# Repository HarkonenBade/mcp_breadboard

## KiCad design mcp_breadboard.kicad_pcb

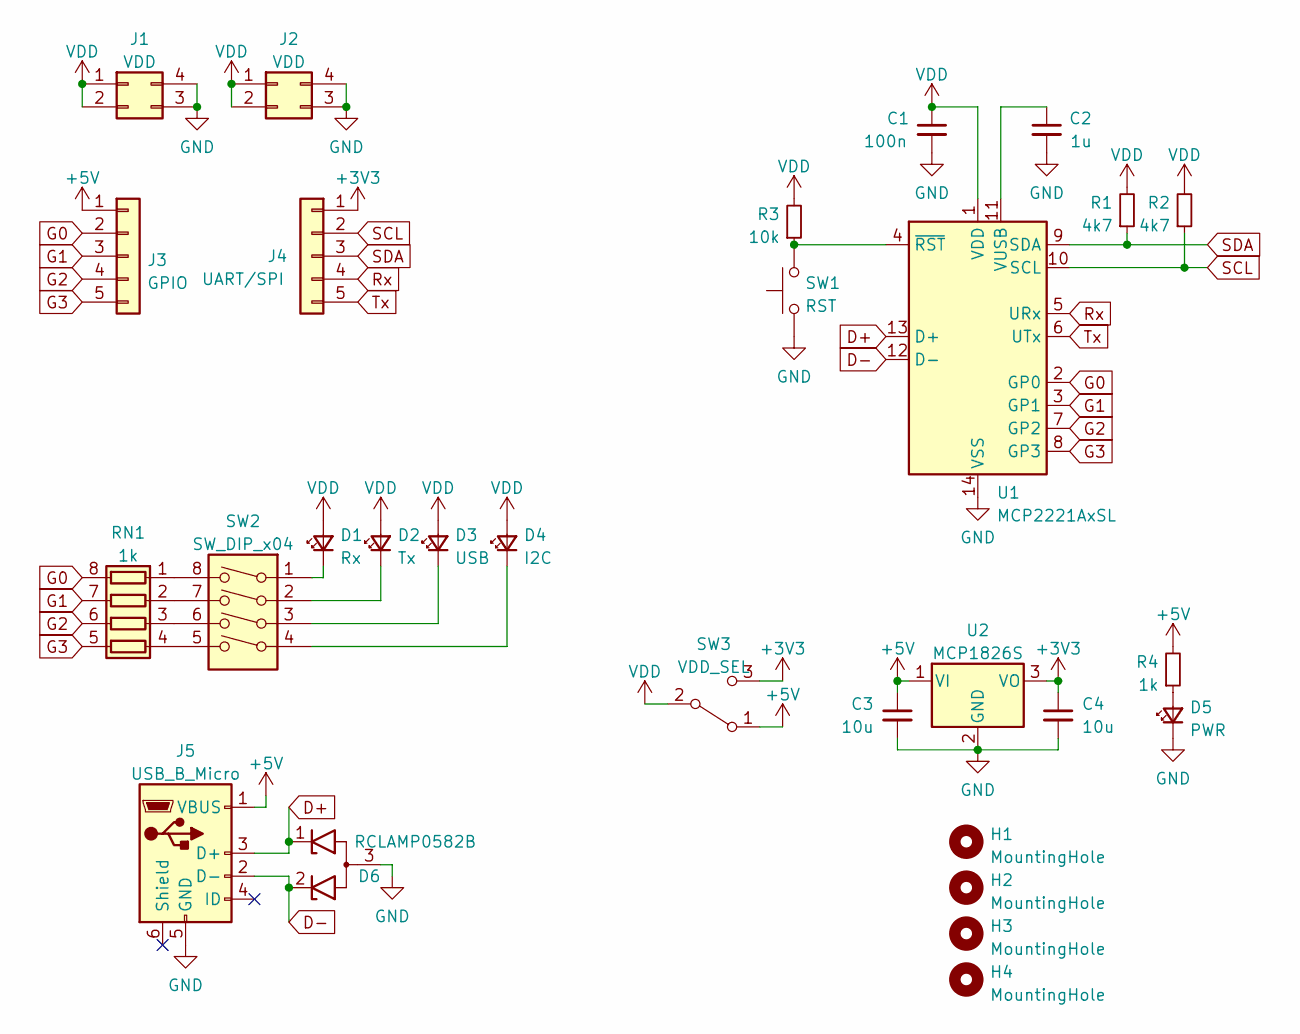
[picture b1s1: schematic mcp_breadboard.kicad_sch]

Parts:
C1: 100n; C_0603_1608Metric
C2: 1u; C_0603_1608Metric
C3, C4: 10u; C_0805_2012Metric; LCSC C1713
D1: Rx; LED_0805_2012Metric
D2: Tx; LED_0805_2012Metric
D3: USB; LED_0805_2012Metric
D4: I2C; LED_0805_2012Metric
D5: PWR; LED_0805_2012Metric
D6: RCLAMP0582B; SOT-523; LCSC C117553
H1, H2, H3, H4: MountingHole; MountingHole_2.7mm_M2.5_ISO7380
J1, J2: VDD; PinHeader_2x02_P2.54mm_Vertical
J3: GPIO; PinHeader_1x05_P2.54mm_Vertical
J4: UART/SPI; PinHeader_1x05_P2.54mm_Vertical
J5: USB_B_Micro; USB_Micro-B_Molex-105017-0001
R1, R2: 4k7; R_0603_1608Metric
R3: 10k; R_0603_1608Metric
R4: 1k; R_0603_1608Metric
RN1: 1k; R_Array_Convex_4x0603; LCSC C425239
SW1: RST; SW_Push_1P1T_NO_6x6mm_H9.5mm; LCSC C493020
SW2: SW_DIP_x04; SW_DIP_SPSTx04_Slide_6.7x11.72mm_W8.61mm_P2.54mm_LowProfile; LCSC C437204
SW3: VDD_SEL; PinHeader_1x03_P2.54mm_Vertical
U1: MCP2221AxSL; SOIC-14_3.9x8.7mm_P1.27mm
U2: MCP1826S; SOT-223-3_TabPin2; LCSC C150719

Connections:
+3V3: C4.1, J4.1, SW3.3 (C), U2.3 (VO)
+5V: C3.1, J3.1, J5.1 (VBUS), R4.2, SW3.1 (A), U2.1 (VI)
D+: D6.1 (K1), J5.3 (D+), U1.13 (D+)
D-: D6.2 (K2), J5.2 (D-), U1.12 (D-)
G0: J3.2, RN1.8 (R1.2), U1.2 (GP0)
G1: J3.3, RN1.7 (R2.2), U1.3 (GP1)
G2: J3.4, RN1.6 (R3.2), U1.7 (GP2)
G3: J3.5, RN1.5 (R4.2), U1.8 (GP3)
GND: C1.2, C2.2, C3.2, C4.2, D5.1 (K), D6.3 (A), J1.3, J1.4, J2.3, J2.4, J5.5 (GND), SW1.1, U1.14 (VSS), U2.2 (GND)
unnamed: C2.1, U1.11 (VUSB)
unnamed: D1.1 (K), SW2.1
unnamed: D2.1 (K), SW2.2
unnamed: D3.1 (K), SW2.3
unnamed: D4.1 (K), SW2.4
unnamed: D5.2 (A), R4.1
unnamed: R3.1, SW1.2, U1.4 (~RST)
unnamed: RN1.1 (R1.1), SW2.8
unnamed: RN1.2 (R2.1), SW2.7
unnamed: RN1.3 (R3.1), SW2.6
unnamed: RN1.4 (R4.1), SW2.5
Rx: J4.4, U1.5 (URx)
SCL: J4.2, R2.1, U1.10 (SCL)
SDA: J4.3, R1.1, U1.9 (SDA)
Tx: J4.5, U1.6 (UTx)
VDD: C1.1, D1.2 (A), D2.2 (A), D3.2 (A), D4.2 (A), J1.1, J1.2, J2.1, J2.2, R1.2, R2.2, R3.2, SW3.2 (B), U1.1 (VDD)

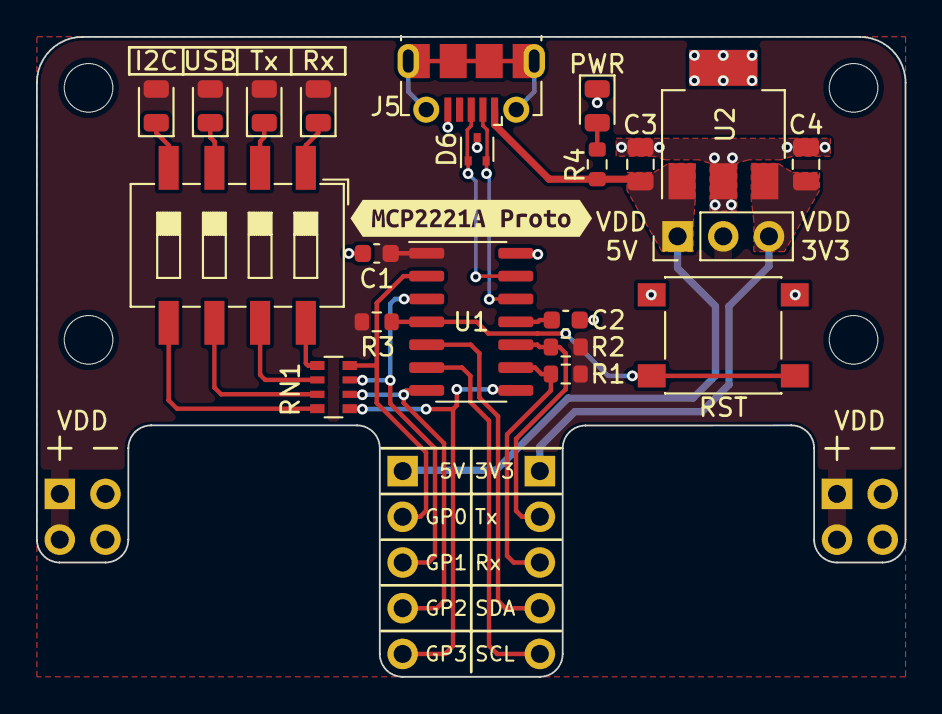
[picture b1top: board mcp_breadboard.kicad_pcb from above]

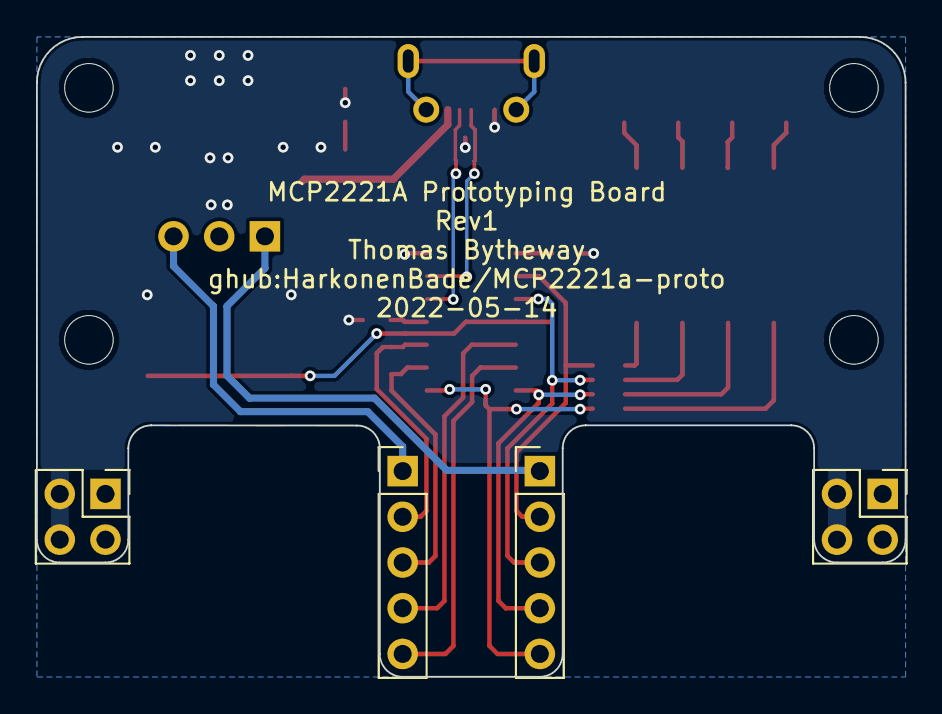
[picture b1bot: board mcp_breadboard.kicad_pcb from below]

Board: 2 copper layers, 48.3 x 35.5 mm, 30 parts (4 on the bottom side), 25 nets.

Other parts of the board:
kibuzzard-627C3F81: G***; kibuzzard-627C3F81

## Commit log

2022-05-12 Initial
2022-05-14 Final rev of design and layout, metrification of major board features for easier laser cutting.
2022-05-14 gerbers
2022-05-15 extra part number
2022-05-16 Final tweaks
2022-05-16 LEDs Moved around
2022-05-18 Final minor board tweaks
2022-05-18 Updated gerbers
2022-05-22 LCSC Part Numbers and BOM
2022-06-09 Fix board outline for breadboard meshing.
